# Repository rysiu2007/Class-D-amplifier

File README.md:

# Class-D Amplifier Learning Project

A discrete $200\text{kHz}$ triangle wave generator and Class-D amplifier stage built for learning analog layout and circuit design. 

## Current Status
* **Simulation:** LTspice transient simulations are verified but yet to finish.
* **Hardware:** KiCad PCB design is currently underway, optimized for single-layer hand-etching.

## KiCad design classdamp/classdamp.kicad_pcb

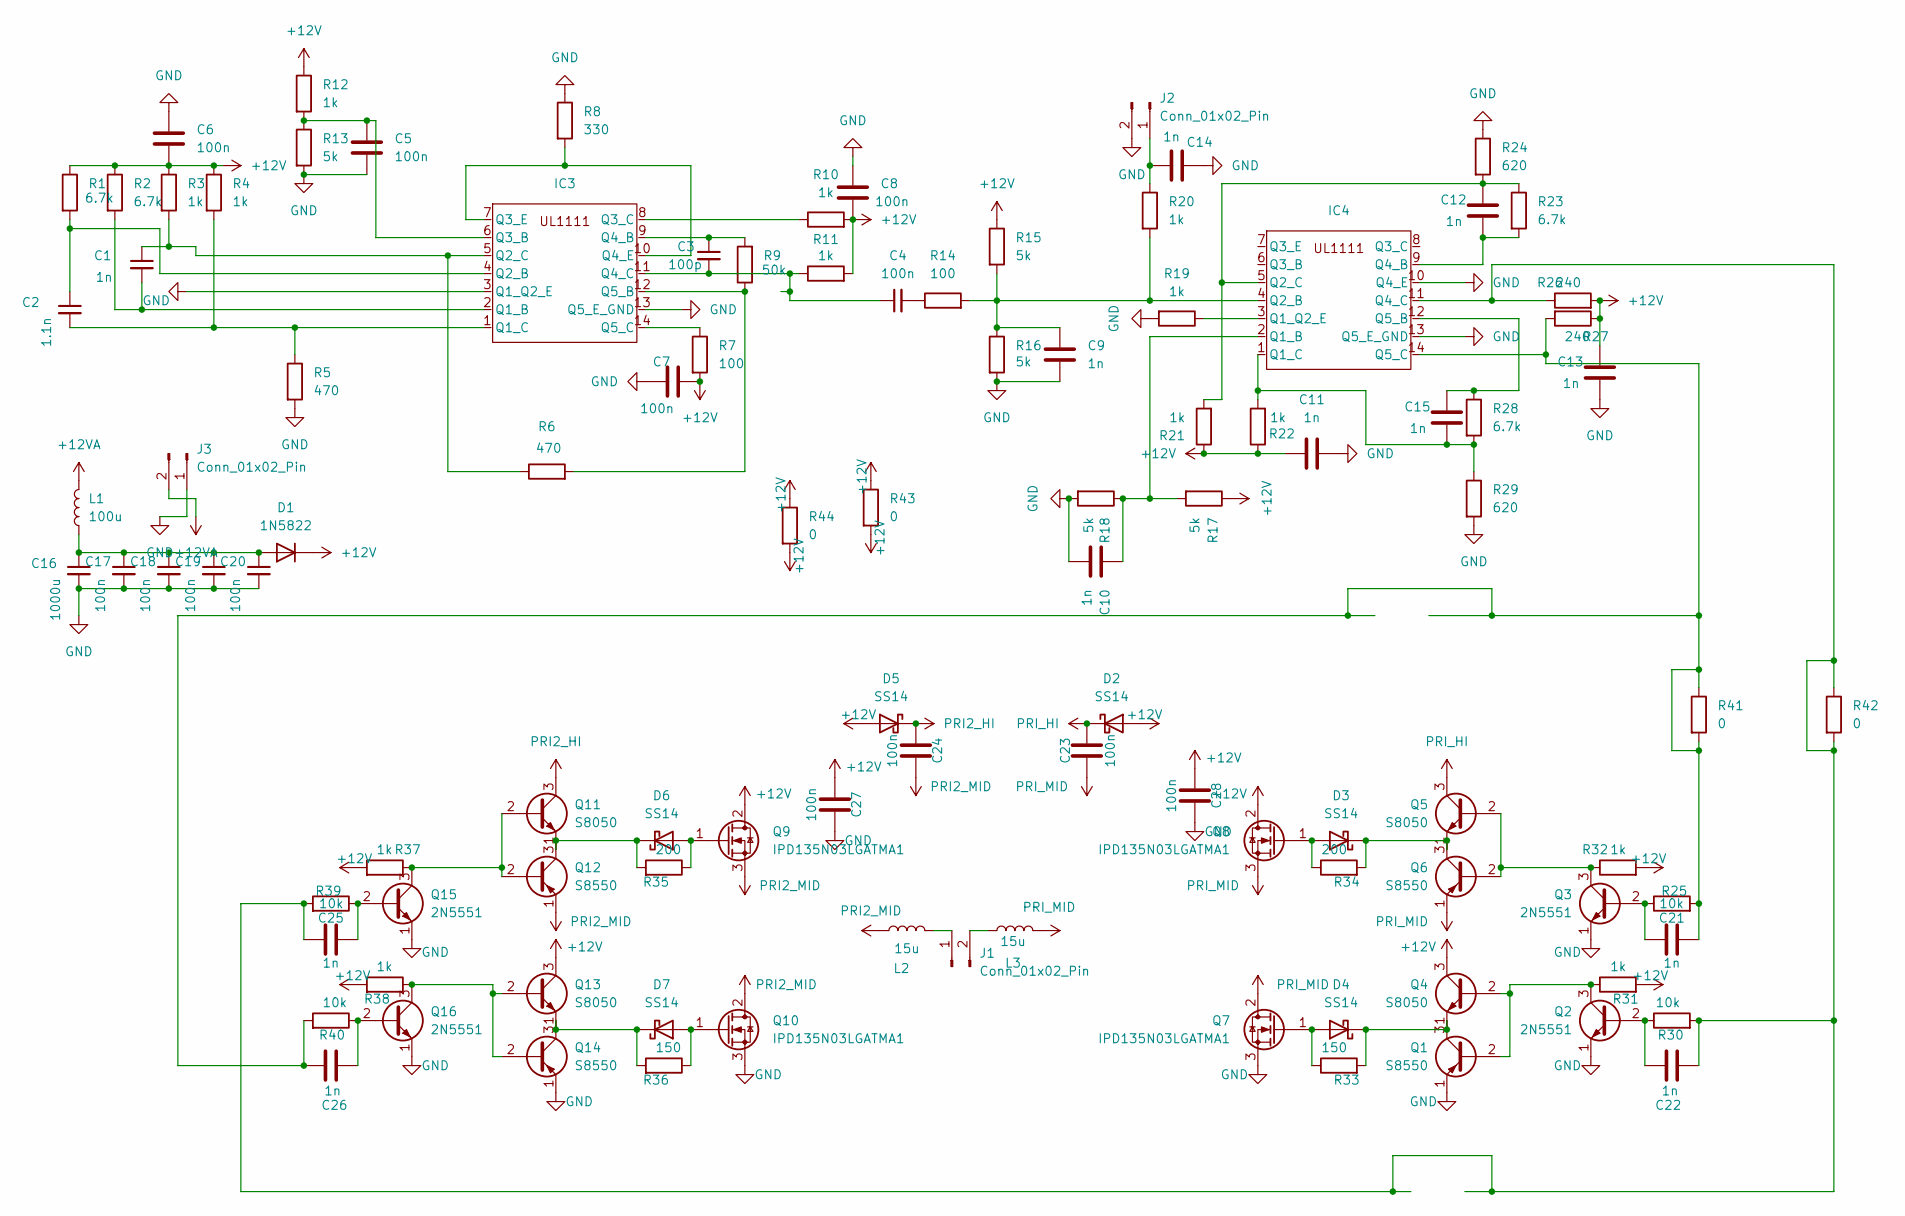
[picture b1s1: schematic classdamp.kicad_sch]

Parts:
C1, C9, C10, C11, C12, C13, C14, C15, C21, C22, C25, C26: 1n; C_Disc_D5.0mm_W2.5mm_P5.00mm
C2: 1.1n; C_Disc_D5.0mm_W2.5mm_P5.00mm
C3: 100p; C_Disc_D5.0mm_W2.5mm_P5.00mm
C4, C5, C6, C7, C8, C17, C18, C19, C20, C23, C24, C27, C28: 100n; C_Disc_D5.0mm_W2.5mm_P5.00mm
C16: 1000u; CP_Radial_D8.0mm_P3.50mm
D1: 1N5822; D_DO-35_SOD27_P7.62mm_Horizontal
D2, D3, D4, D5, D6, D7: SS14; D_SMA_Handsoldering
IC3, IC4: DIP-14_W7.62mm
J1, J2, J3: Conn_01x02_Pin; JWT_A3963_1x02_P3.96mm_Vertical
L1: 100u; L_Toroid_Horizontal_D24.1mm_P23.10mm_Bourns_2200
L2, L3: 15u; L_Radial_D10.0mm_P5.00mm_Fastron_07M
Q1, Q6, Q12, Q14: S8550; TO-92_Inline
Q2, Q3, Q15, Q16: 2N5551; TO-92_Inline
Q4, Q5, Q11, Q13: S8050; TO-92_Inline
Q7, Q8, Q9, Q10: IPD135N03LGATMA1; TO-252-2
R1, R2, R23, R28: 6.7k; R_Axial_DIN0207_L6.3mm_D2.5mm_P15.24mm_Horizontal
R3, R4, R10, R11, R12, R19, R20, R21, R22: 1k; R_Axial_DIN0207_L6.3mm_D2.5mm_P15.24mm_Horizontal
R5, R6: 470; R_Axial_DIN0207_L6.3mm_D2.5mm_P15.24mm_Horizontal
R7, R14: 100; R_Axial_DIN0207_L6.3mm_D2.5mm_P15.24mm_Horizontal
R8: 330; R_Axial_DIN0207_L6.3mm_D2.5mm_P15.24mm_Horizontal
R9: 50k; R_Axial_DIN0207_L6.3mm_D2.5mm_P15.24mm_Horizontal
R13, R15, R16, R17, R18: 5k; R_Axial_DIN0207_L6.3mm_D2.5mm_P15.24mm_Horizontal
R24, R29: 620; R_Axial_DIN0207_L6.3mm_D2.5mm_P15.24mm_Horizontal
R25, R30, R39, R40: 10k; R_Axial_DIN0204_L3.6mm_D1.6mm_P2.54mm_Vertical
R26, R27: 240; R_Axial_DIN0207_L6.3mm_D2.5mm_P15.24mm_Horizontal
R31, R32, R37, R38: 1k; R_Axial_DIN0204_L3.6mm_D1.6mm_P2.54mm_Vertical
R33, R36: 150; R_Axial_DIN0204_L3.6mm_D1.6mm_P2.54mm_Vertical
R34, R35: 200; R_Axial_DIN0204_L3.6mm_D1.6mm_P2.54mm_Vertical
R41, R42, R43, R44: 0; R_Axial_DIN0207_L6.3mm_D2.5mm_P15.24mm_Horizontal

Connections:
+12V: C6.2, C7.2, C8.2, C11.1, C13.1, C27.2, C28.2, D1.1 (K), D2.2 (A), D5.2 (A), Q4.3 (C), Q8.2 (D), Q9.2 (D), Q13.3 (C), R1.1, R2.1, R3.1, R4.1, R7.2, R10.2, R11.2, R12.1, R15.1, R17.1, R21.1, R22.1, R26.2, R27.1, R31.2, R32.2, R37.2, R38.2, R43.1, R43.2, R44.1, R44.2
+12VA: J3.2, L1.2
GND: C5.2, C6.1, C7.1, C8.1, C9.2, C10.2, C11.2, C13.2, C14.1, C16.2, C17.2, C18.2, C19.2, C20.2, C27.1, C28.1, IC3.3 (Q1_Q2_E), IC3.13 (Q5_E_GND), IC4.10 (Q4_E), IC4.13 (Q5_E_GND), J2.2, J3.1, Q1.1 (E), Q2.1 (E), Q3.1 (E), Q7.3 (S), Q10.3 (S), Q14.1 (E), Q15.1 (E), Q16.1 (E), R5.2, R8.1, R13.2, R16.2, R18.2, R19.2, R24.1, R29.2
unnamed: C4.2, R14.1
unnamed: C16.1, C17.1, C18.1, C19.1, C20.1, D1.2 (A), L1.1
unnamed: D3.2 (A), Q8.1 (G), R34.1
unnamed: D3.1 (K), Q5.1 (E), Q6.3 (C), R34.2
unnamed: D4.2 (A), Q7.1 (G), R33.1
unnamed: D4.1 (K), Q1.3 (C), Q4.1 (E), R33.2
unnamed: D6.2 (A), Q9.1 (G), R35.1
unnamed: D6.1 (K), Q11.1 (E), Q12.3 (C), R35.2
unnamed: D7.2 (A), Q10.1 (G), R36.1
unnamed: D7.1 (K), Q13.1 (E), Q14.3 (C), R36.2
unnamed: C1.2, IC3.2 (Q1_B), R2.2
unnamed: C2.2, IC3.1 (Q1_C), R4.2, R5.1
unnamed: C2.1, IC3.4 (Q2_B), R1.2
unnamed: C1.1, IC3.5 (Q2_C), R3.2, R6.1
unnamed: C5.1, IC3.6 (Q3_B), R12.2, R13.1
unnamed: IC3.8 (Q3_C), R10.1
unnamed: IC3.7 (Q3_E), IC3.10 (Q4_E), R8.2
unnamed: C3.1, IC3.9 (Q4_B), R9.2
unnamed: C3.2, C4.1, IC3.11 (Q4_C), R11.1
unnamed: IC3.12 (Q5_B), R6.2, R9.1
unnamed: IC3.14 (Q5_C), R7.1
unnamed: C10.1, IC4.2 (Q1_B), R17.2, R18.1
unnamed: C15.2, IC4.1 (Q1_C), R22.2, R28.2, R29.1
unnamed: IC4.3 (Q1_Q2_E), R19.1
unnamed: C9.1, IC4.4 (Q2_B), R14.2, R15.2, R16.1, R20.2
unnamed: C12.1, IC4.5 (Q2_C), R21.2, R23.1, R24.2
unnamed: C12.2, IC4.9 (Q4_B), R23.2
unnamed: C22.2, C25.2, IC4.11 (Q4_C), R26.1, R30.2, R39.2, R42.1, R42.2
unnamed: C15.1, IC4.12 (Q5_B), R28.1
unnamed: C21.2, C26.2, IC4.14 (Q5_C), R25.2, R27.2, R40.2, R41.1, R41.2
unnamed: J1.1, L2.2
unnamed: J1.2, L3.1
unnamed: C14.2, J2.1, R20.1
unnamed: Q1.2 (B), Q2.3 (C), Q4.2 (B), R31.1
unnamed: C22.1, Q2.2 (B), R30.1
unnamed: C21.1, Q3.2 (B), R25.1
unnamed: Q3.3 (C), Q5.2 (B), Q6.2 (B), R32.1
unnamed: Q11.2 (B), Q12.2 (B), Q15.3 (C), R37.1
unnamed: Q13.2 (B), Q14.2 (B), Q16.3 (C), R38.1
unnamed: C25.1, Q15.2 (B), R39.1
unnamed: C26.1, Q16.2 (B), R40.1
PRI2_HI: C24.2, D5.1 (K), Q11.3 (C)
PRI2_MID: C24.1, L2.1, Q9.3 (S), Q10.2 (D), Q12.1 (E)
PRI_HI: C23.2, D2.1 (K), Q5.3 (C)
PRI_MID: C23.1, L3.2, Q6.1 (E), Q7.2 (D), Q8.3 (S)

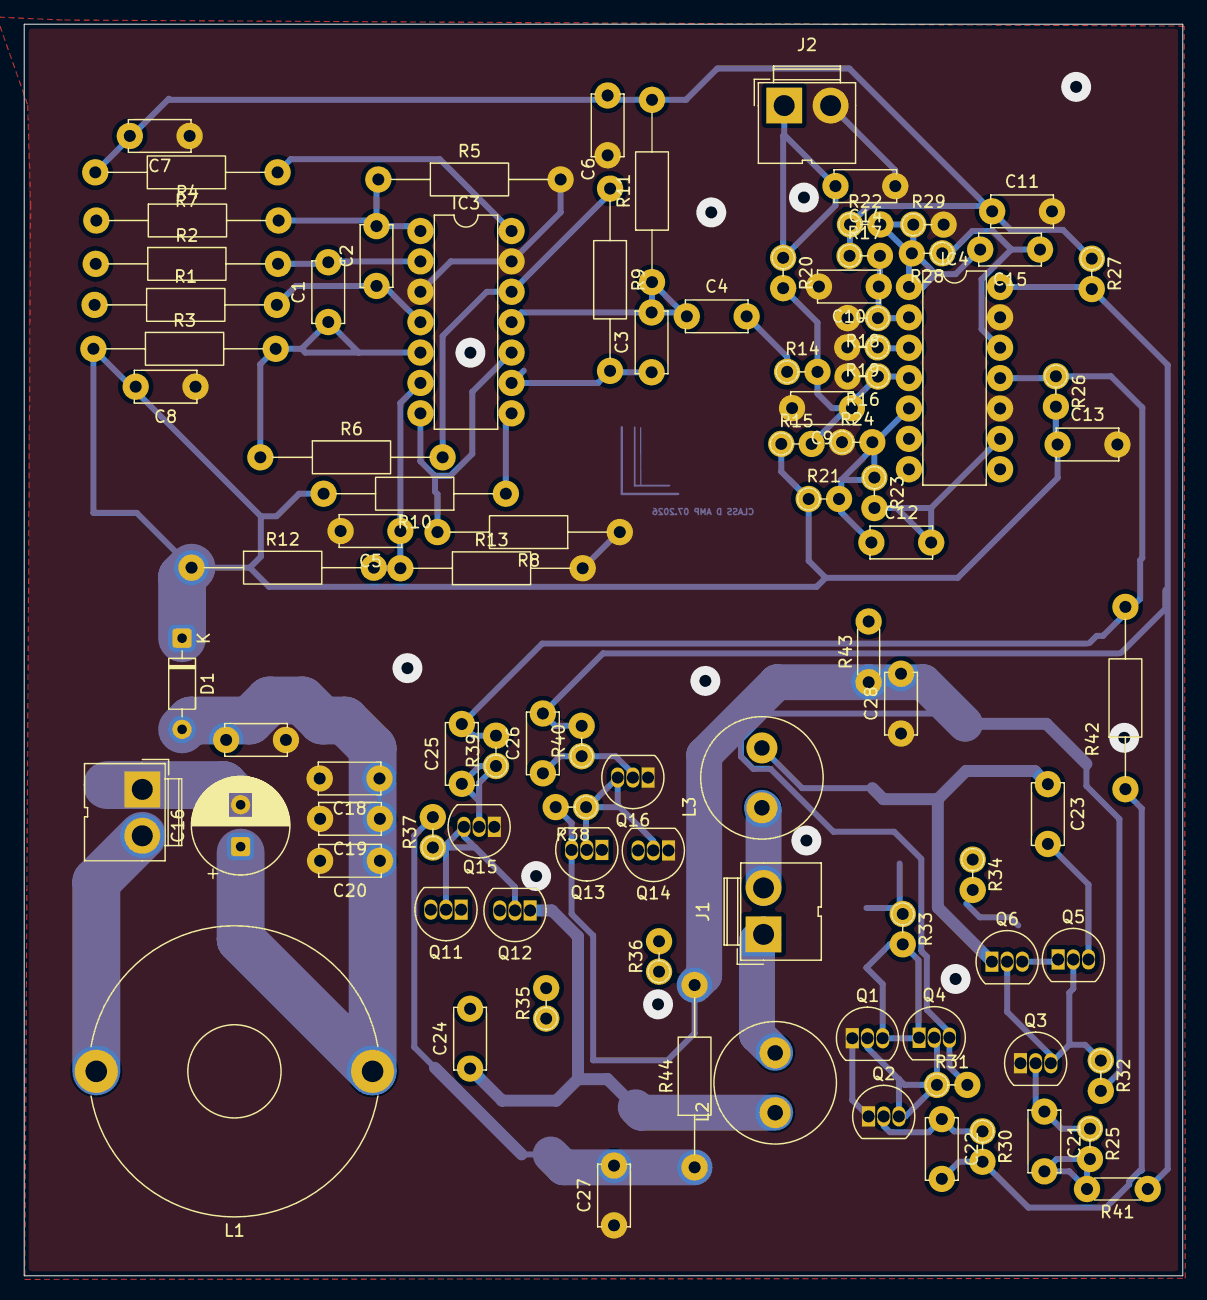
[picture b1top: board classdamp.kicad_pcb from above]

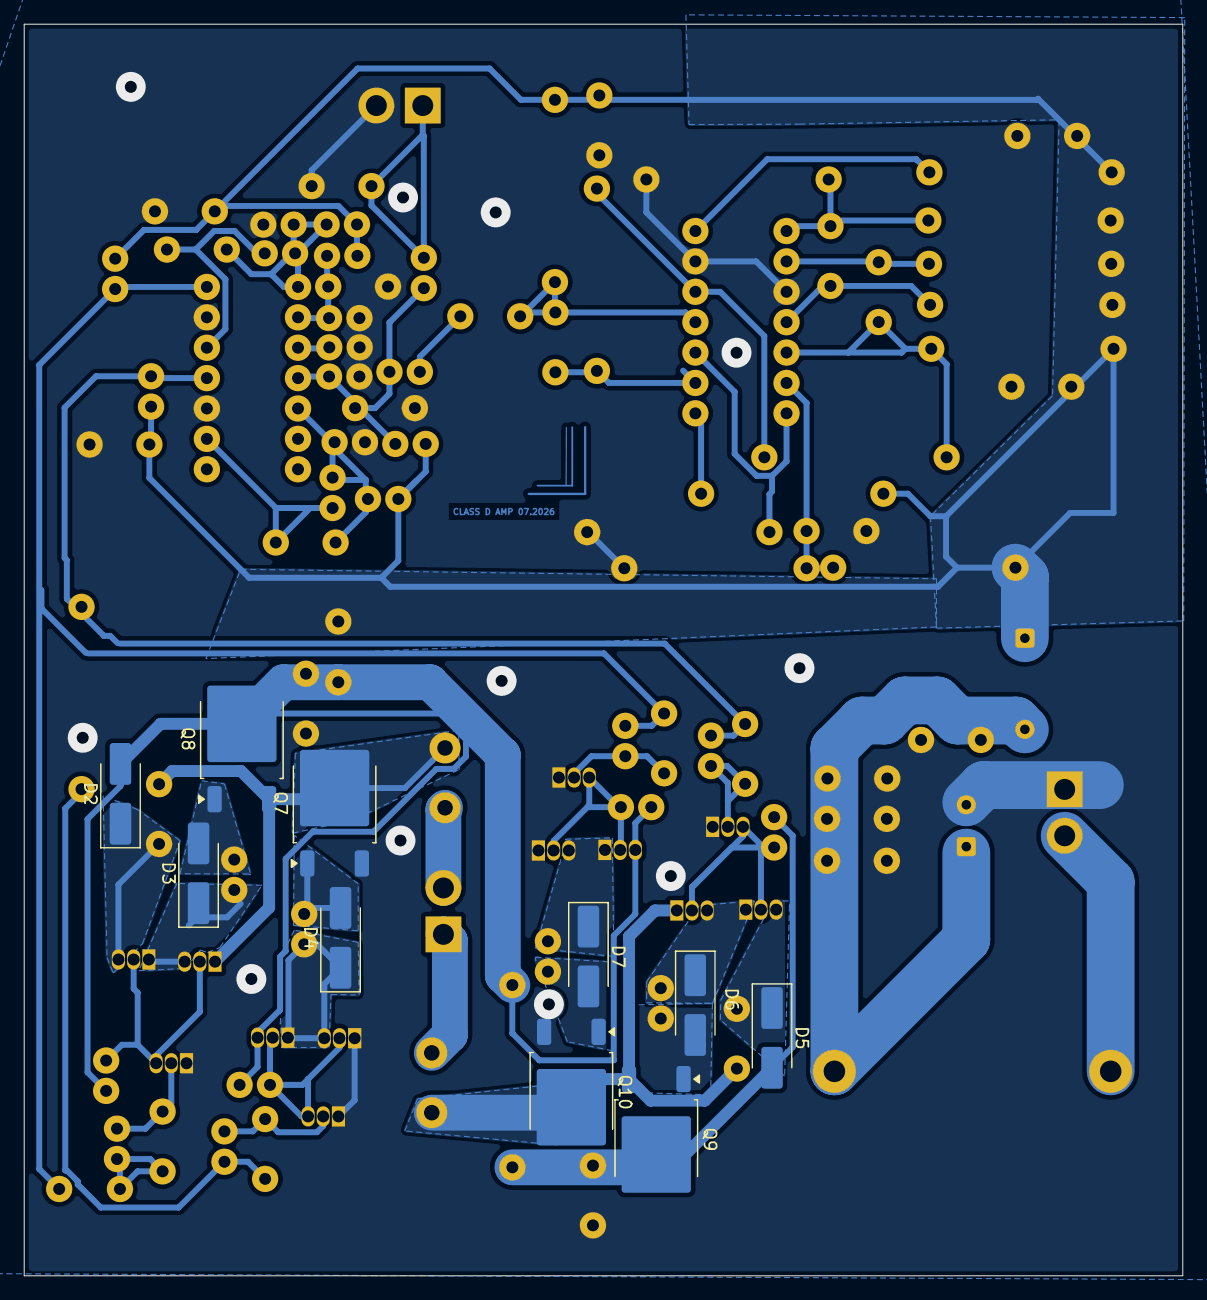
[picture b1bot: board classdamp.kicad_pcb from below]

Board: 2 copper layers, 96.9 x 104.6 mm, 103 parts (10 on the bottom side), 48 nets.
